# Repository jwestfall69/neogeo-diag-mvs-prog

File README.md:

# neogeo-diag-mvs-prog

## Overview
This is a custom NeoGeo MVS Prog board that is used in conjunction with the [NeoGeo Diag Bios](https://github.com/jwestfall69/neogeo-diag-bios) that allows for testing the P ROM address and data buses between the motherboard and the cart slot.  Its meant to help trouble shoot getting a crosshatch screen or if your game cart boots then crashes after a while (possible faulty P ROM bank switching).

It works by using an SRAM chip instead of a ROM for the program rom on the PROG board.  Doing this allows the diag bios to run tests on it similar to that of work ram to find issues.

Its not possible to test all lines related to the program rom, so there are 3 leds at the top of the board.  These 3 LEDs (ROMOE, PORTADDR, SLOTCS) should be lit up when the P ROM Bus tests are running in the diag bios.

<br>

## PCB Manufacturing
PCB should be 1.6mm thickness.  With these boards likely being inserted and removed numerous times its suggested you use ENIG surface finishing and gold fingers w/45 degree chamfering.

I've been using [jlcpcb](https://jlcpcb.com/) for PCB manufacturing.  Just watch out that by default they will add an order number to the silk screen unless you tell them not to.

## BOM
| Quantity | Description | Part Number | Digikey | Notes |
|:--------:|:------------|-------------|---------|-------|
| 1        | SRAM 8Mbit 44 pin TSOP II | AS6C8016-55ZIN | [1450-1041-ND](https://www.digikey.com/en/products/detail/alliance-memory-inc/AS6C8016-55ZIN/4234600) | |
| 1        | 74LS04 pin 14 SOIC | SN74LS04DR | [296-14875-2-ND](https://www.digikey.com/en/products/detail/texas-instruments/SN74LS04DR/562927) | |
| 1        | 74LS08 pin 14 SOIC | SN74LS08DR | [296-14879-2-ND](https://www.digikey.com/en/products/detail/texas-instruments/SN74LS08DR/562906) | |
| 1        | 74LS11 pin 14 SOIC | SN74LS11DR | [296-28984-2-ND](https://www.digikey.com/en/products/detail/texas-instruments/SN74LS11DR/1571760) | |
| 5        | 100nf / 0.1uf Ceramic Capacitor 0805 Size | CL21B104KBCNNNC | [1276-1003-2-ND](https://www.digikey.com/en/products/detail/samsung-electro-mechanics/CL21B104KBCNNNC/3886661) | Any 100nf 0805 is fine |
| 3        | 1K Ohm resistor 0805 Size | ERJ-6GEYJ102V | [P1.0KACT-ND](https://www.digikey.com/en/products/detail/panasonic-electronic-components/ERJ-6GEYJ102V/83014) | Any 1K 0805 resistor is fine |
| 3        | Green LED 0805 12mcd | LTST-C171GKT | [160-1423-2-ND](https://www.digikey.com/en/products/detail/liteon/LTST-C171GKT/386793) | Other 0805 size LEDs should be fine |

## Assembly
The SRAM has a really fine pin pitch, so take your time.  Other then that nothing special.

## Usage
The prog board should be used along with a valid CHA board.  Ideally you probably want a full diag cart where the CHA board has the M1 diag rom and this PROG board.  The cart should be inserted into the slot and then boot the board with the diag bios. Goto the main menu screen.

Pick: ```P ROM BUS TESTS (CUSTOM CART)```

If you have a multi-slot board you can use the left/right on the joystick to change the slot number the test will run on.  Then press A+C to start the tests or D to go back to the main menu.

In the event you pick the wrong/empty slot and you get a white screen you can press D to stop the test.  This should also fix your screen as it will switch back to the onboard sfix rom for text.

The tests will run continually until D is pressed or an issue is detected.  While the tests are running you should expect the 3 LEDs on the PROG board to be lit up.

If you attempt to run the P rom bus tests without the diag PROG board you will get a ```P2 UNWRITABLE (LOWER)``` error.

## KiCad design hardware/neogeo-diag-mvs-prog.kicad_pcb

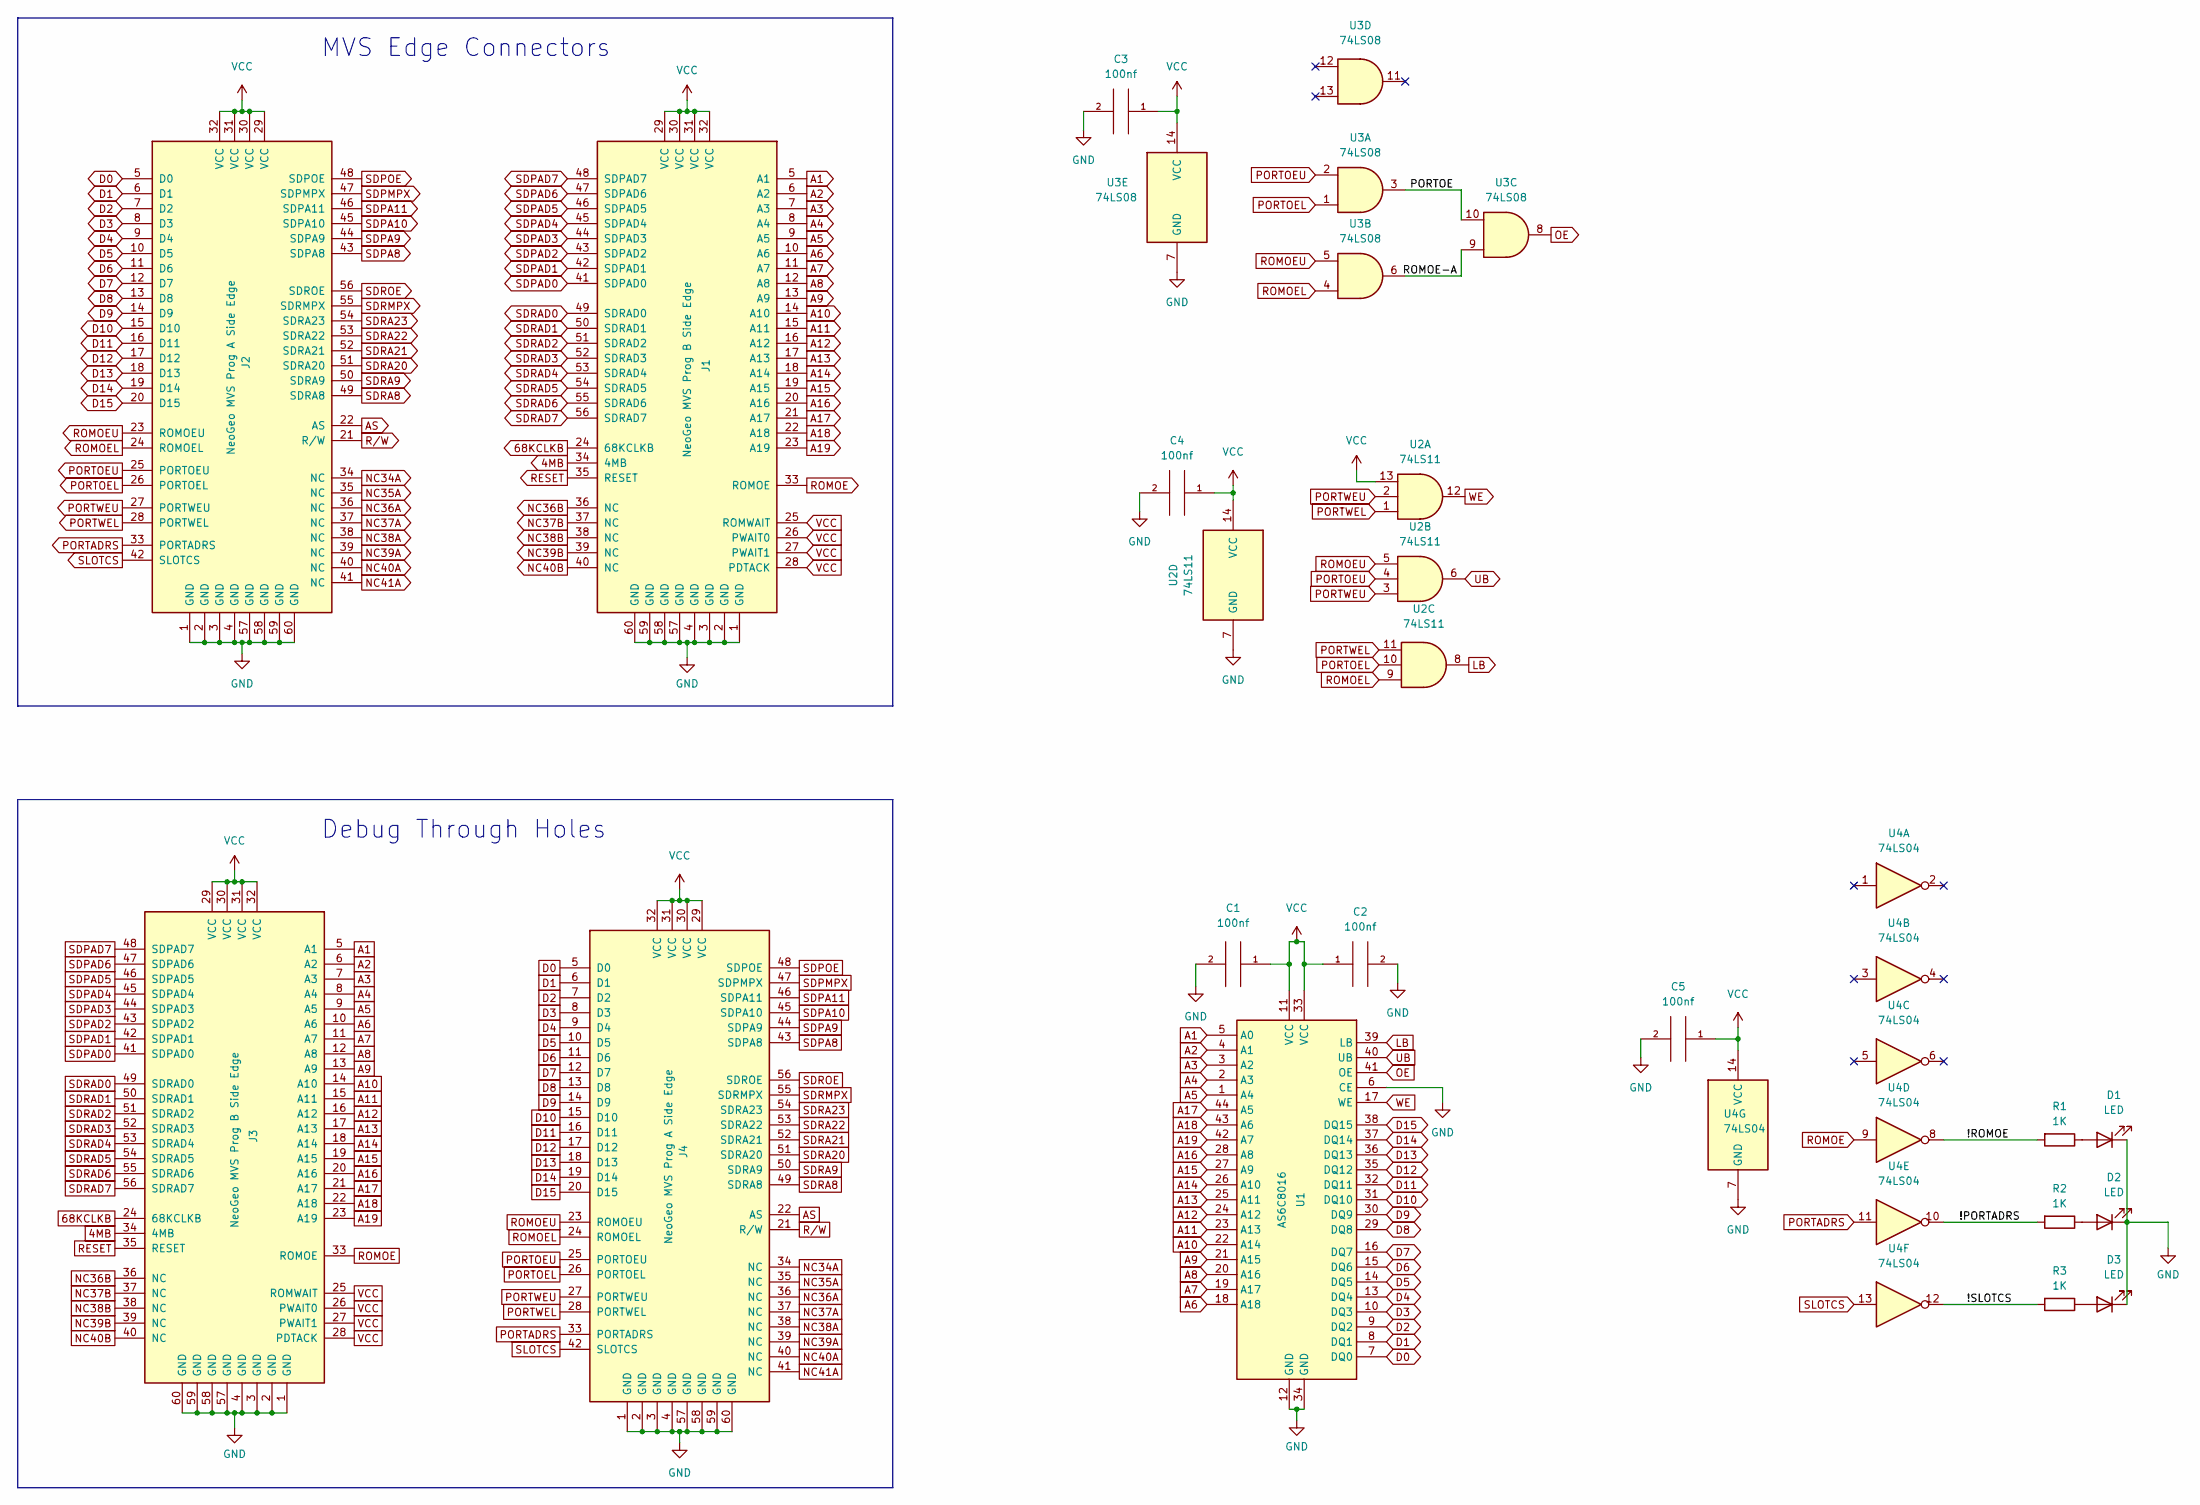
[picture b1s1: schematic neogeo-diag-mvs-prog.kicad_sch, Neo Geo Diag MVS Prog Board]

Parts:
C1, C2, C3, C4, C5: 100nf; C_0805_2012Metric
D1, D2, D3: LED; LED_0805_2012Metric
J1: NeoGeo MVS Prog B Side Edge; neogeo-mvs-prog-b-side-edge
J2: NeoGeo MVS Prog A Side Edge; neogeo-mvs-prog-a-side-edge
J3: NeoGeo MVS Prog B Side Edge; neogeo-mvs-prog-edge-test-points
J4: NeoGeo MVS Prog A Side Edge; neogeo-mvs-prog-edge-test-points
R1, R2, R3: 1K; R_0805_2012Metric
U1: AS6C8016; TSOP-II-44_10.16x18.41mm_P0.8mm
U2: 74LS11; SO-14_3.9x8.65mm_P1.27mm
U3: 74LS08; SO-14_3.9x8.65mm_P1.27mm
U4: 74LS04

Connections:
4MB: J1.34 (4MB), J3.34 (4MB)
68KCLKB: J1.24 (68KCLKB), J3.24 (68KCLKB)
/!PORTADRS: R2.2, U4.10
/!ROMOE: R1.2, U4.8
/!SLOTCS: R3.2, U4.12
/PORTOE: U3.3, U3.10
/ROMOE-A: U3.6, U3.9
A1: J1.5 (A1), J3.5 (A1), U1.5 (A0)
A2: J1.6 (A2), J3.6 (A2), U1.4 (A1)
A3: J1.7 (A3), J3.7 (A3), U1.3 (A2)
A4: J1.8 (A4), J3.8 (A4), U1.2 (A3)
A5: J1.9 (A5), J3.9 (A5), U1.1 (A4)
A6: J1.10 (A6), J3.10 (A6), U1.18 (A18)
A7: J1.11 (A7), J3.11 (A7), U1.19 (A17)
A8: J1.12 (A8), J3.12 (A8), U1.20 (A16)
A9: J1.13 (A9), J3.13 (A9), U1.21 (A15)
A10: J1.14 (A10), J3.14 (A10), U1.22 (A14)
A11: J1.15 (A11), J3.15 (A11), U1.23 (A13)
A12: J1.16 (A12), J3.16 (A12), U1.24 (A12)
A13: J1.17 (A13), J3.17 (A13), U1.25 (A11)
A14: J1.18 (A14), J3.18 (A14), U1.26 (A10)
A15: J1.19 (A15), J3.19 (A15), U1.27 (A9)
A16: J1.20 (A16), J3.20 (A16), U1.28 (A8)
A17: J1.21 (A17), J3.21 (A17), U1.44 (A5)
A18: J1.22 (A18), J3.22 (A18), U1.43 (A6)
A19: J1.23 (A19), J3.23 (A19), U1.42 (A7)
AS: J2.22 (AS), J4.22 (AS)
D0: J2.5 (D0), J4.5 (D0), U1.7 (DQ0)
D1: J2.6 (D1), J4.6 (D1), U1.8 (DQ1)
D2: J2.7 (D2), J4.7 (D2), U1.9 (DQ2)
D3: J2.8 (D3), J4.8 (D3), U1.10 (DQ3)
D4: J2.9 (D4), J4.9 (D4), U1.13 (DQ4)
D5: J2.10 (D5), J4.10 (D5), U1.14 (DQ5)
D6: J2.11 (D6), J4.11 (D6), U1.15 (DQ6)
D7: J2.12 (D7), J4.12 (D7), U1.16 (DQ7)
D8: J2.13 (D8), J4.13 (D8), U1.29 (DQ8)
D9: J2.14 (D9), J4.14 (D9), U1.30 (DQ9)
D10: J2.15 (D10), J4.15 (D10), U1.31 (DQ10)
D11: J2.16 (D11), J4.16 (D11), U1.32 (DQ11)
D12: J2.17 (D12), J4.17 (D12), U1.35 (DQ12)
D13: J2.18 (D13), J4.18 (D13), U1.36 (DQ13)
D14: J2.19 (D14), J4.19 (D14), U1.37 (DQ14)
D15: J2.20 (D15), J4.20 (D15), U1.38 (DQ15)
GND: C1.2, C2.2, C3.2, C4.2, C5.2, D1.1 (K), D2.1 (K), D3.1 (K), J1.1 (GND), J1.2 (GND), J1.3 (GND), J1.4 (GND), J1.57 (GND), J1.58 (GND), J1.59 (GND), J1.60 (GND), J2.1 (GND), J2.2 (GND), J2.3 (GND), J2.4 (GND), J2.57 (GND), J2.58 (GND), J2.59 (GND), J2.60 (GND), J3.1 (GND), J3.2 (GND), J3.3 (GND), J3.4 (GND), J3.57 (GND), J3.58 (GND), J3.59 (GND), J3.60 (GND), J4.1 (GND), J4.2 (GND), J4.3 (GND), J4.4 (GND), J4.57 (GND), J4.58 (GND), J4.59 (GND), J4.60 (GND), U1.6 (CE), U1.12 (GND), U1.34 (GND), U2.7 (GND), U3.7 (GND), U4.7 (GND)
LB: U1.39 (LB), U2.8
NC34A: J2.34 (NC), J4.34 (NC)
NC35A: J2.35 (NC), J4.35 (NC)
NC36A: J2.36 (NC), J4.36 (NC)
NC36B: J1.36 (NC), J3.36 (NC)
NC37A: J2.37 (NC), J4.37 (NC)
NC37B: J1.37 (NC), J3.37 (NC)
NC38A: J2.38 (NC), J4.38 (NC)
NC38B: J1.38 (NC), J3.38 (NC)
NC39A: J2.39 (NC), J4.39 (NC)
NC39B: J1.39 (NC), J3.39 (NC)
NC40A: J2.40 (NC), J4.40 (NC)
NC40B: J1.40 (NC), J3.40 (NC)
NC41A: J2.41 (NC), J4.41 (NC)
unnamed: D1.2 (A), R1.1
unnamed: D2.2 (A), R2.1
unnamed: D3.2 (A), R3.1
OE: U1.41 (OE), U3.8
PORTADRS: J2.33 (PORTADRS), J4.33 (PORTADRS), U4.11
PORTOEL: J2.26 (PORTOEL), J4.26 (PORTOEL), U2.10, U3.1
PORTOEU: J2.25 (PORTOEU), J4.25 (PORTOEU), U2.4, U3.2
PORTWEL: J2.28 (PORTWEL), J4.28 (PORTWEL), U2.1, U2.11
PORTWEU: J2.27 (PORTWEU), J4.27 (PORTWEU), U2.2, U2.3
RESET: J1.35 (RESET), J3.35 (RESET)
ROMOE: J1.33 (ROMOE), J3.33 (ROMOE), U4.9
ROMOEL: J2.24 (ROMOEL), J4.24 (ROMOEL), U2.9, U3.4
ROMOEU: J2.23 (ROMOEU), J4.23 (ROMOEU), U2.5, U3.5
R/W: J2.21 (R/W), J4.21 (R/W)
SDPA8: J2.43 (SDPA8), J4.43 (SDPA8)
SDPA9: J2.44 (SDPA9), J4.44 (SDPA9)
SDPA10: J2.45 (SDPA10), J4.45 (SDPA10)
SDPA11: J2.46 (SDPA11), J4.46 (SDPA11)
SDPAD0: J1.41 (SDPAD0), J3.41 (SDPAD0)
SDPAD1: J1.42 (SDPAD1), J3.42 (SDPAD1)
SDPAD2: J1.43 (SDPAD2), J3.43 (SDPAD2)
SDPAD3: J1.44 (SDPAD3), J3.44 (SDPAD3)
SDPAD4: J1.45 (SDPAD4), J3.45 (SDPAD4)
SDPAD5: J1.46 (SDPAD5), J3.46 (SDPAD5)
SDPAD6: J1.47 (SDPAD6), J3.47 (SDPAD6)
SDPAD7: J1.48 (SDPAD7), J3.48 (SDPAD7)
SDPMPX: J2.47 (SDPMPX), J4.47 (SDPMPX)
SDPOE: J2.48 (SDPOE), J4.48 (SDPOE)
SDRA8: J2.49 (SDRA8), J4.49 (SDRA8)
SDRA9: J2.50 (SDRA9), J4.50 (SDRA9)
SDRA20: J2.51 (SDRA20), J4.51 (SDRA20)
SDRA21: J2.52 (SDRA21), J4.52 (SDRA21)
SDRA22: J2.53 (SDRA22), J4.53 (SDRA22)
SDRA23: J2.54 (SDRA23), J4.54 (SDRA23)
SDRAD0: J1.49 (SDRAD0), J3.49 (SDRAD0)
SDRAD1: J1.50 (SDRAD1), J3.50 (SDRAD1)
SDRAD2: J1.51 (SDRAD2), J3.51 (SDRAD2)
SDRAD3: J1.52 (SDRAD3), J3.52 (SDRAD3)
SDRAD4: J1.53 (SDRAD4), J3.53 (SDRAD4)
SDRAD5: J1.54 (SDRAD5), J3.54 (SDRAD5)
SDRAD6: J1.55 (SDRAD6), J3.55 (SDRAD6)
SDRAD7: J1.56 (SDRAD7), J3.56 (SDRAD7)
SDRMPX: J2.55 (SDRMPX), J4.55 (SDRMPX)
SDROE: J2.56 (SDROE), J4.56 (SDROE)
SLOTCS: J2.42 (SLOTCS), J4.42 (SLOTCS), U4.13
UB: U1.40 (UB), U2.6
VCC: C1.1, C2.1, C3.1, C4.1, C5.1, J1.25 (ROMWAIT), J1.26 (PWAIT0), J1.27 (PWAIT1), J1.28 (PDTACK), J1.29 (VCC), J1.30 (VCC), J1.31 (VCC), J1.32 (VCC), J2.29 (VCC), J2.30 (VCC), J2.31 (VCC), J2.32 (VCC), J3.25 (ROMWAIT), J3.26 (PWAIT0), J3.27 (PWAIT1), J3.28 (PDTACK), J3.29 (VCC), J3.30 (VCC), J3.31 (VCC), J3.32 (VCC), J4.29 (VCC), J4.30 (VCC), J4.31 (VCC), J4.32 (VCC), U1.11 (VCC), U1.33 (VCC), U2.13, U2.14 (VCC), U3.14 (VCC), U4.14 (VCC)
WE: U1.17 (WE), U2.12

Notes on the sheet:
Debug Through Holes
MVS Edge Connectors

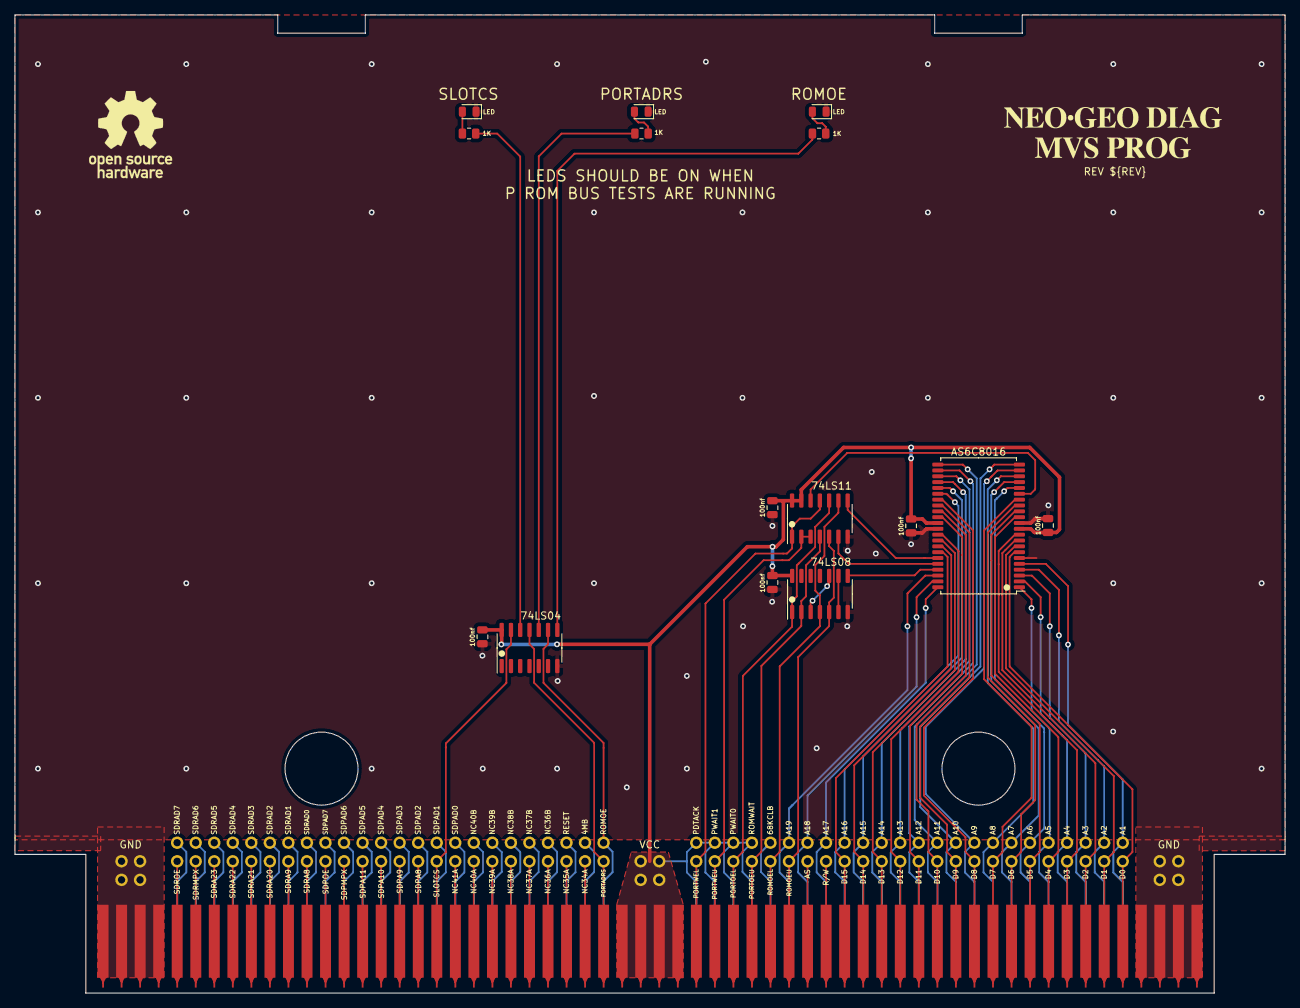
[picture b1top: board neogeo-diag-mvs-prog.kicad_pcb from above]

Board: 2 copper layers, 174.0 x 134.0 mm, 19 parts (1 on the bottom side), 106 nets.

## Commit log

2023-02-25 Skeleton
2023-02-25 fix up neogeo-diag-kicad-library submodule
2023-02-25 Check in of board
2023-02-27 Fixes: directions in schematic, non-straight edge-cut
2023-02-28 Fix solder mask exclude on edge connector
2023-03-01 Lower edge connector pads a little bit
2023-03-01 Fix edge connector not being 100% centered
2023-03-01 Tweak solder mask exclude on edge connector
2023-03-02 Move leds so they are near the top of the board
2023-03-07 Make power traces be 0.5mm, adjustment to some of the text
2023-03-11 Pull in newer neogeo-diag-kicad-library
2023-03-11 Add logo
2023-03-11 Adjust output dir
2023-03-25 Docs
